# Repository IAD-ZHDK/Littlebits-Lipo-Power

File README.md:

# Littlebits Lipo Power

**A power-bit for running littlebits projects on a standard 3.7 Lipo battery with 2-pin, PH series JST connection.**

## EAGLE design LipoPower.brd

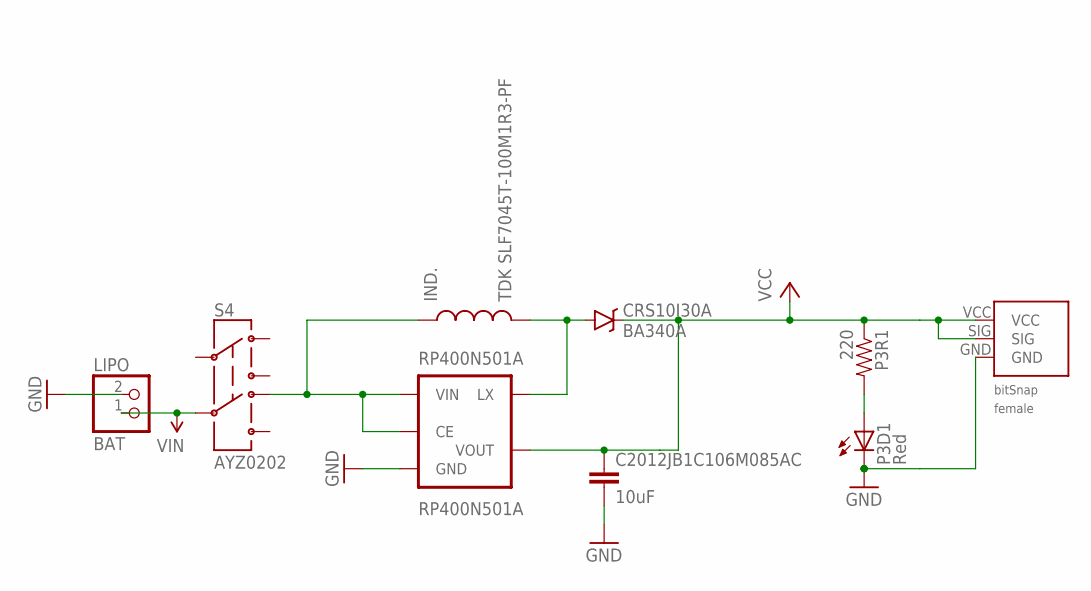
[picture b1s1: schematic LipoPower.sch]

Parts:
C2012JB1C106M085AC: 10uF; 1210
CRS10I30A: BA340A; SMA-DIODE
IND.: TDK SLF7045T-100M1R3-PF; B82462G
LIPO: BAT; JST-PH-2-SMT-RA
P3BSF1: BITSNAP_V03_FEMALE
P3D1: Red; LED-1206
P3R1: 220; 0603-RES
RP400N501A: RP400N501A; SOT23-5
S4: AYZ0202

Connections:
GND: C2012JB1C106M085AC.2, LIPO.2 (1), P3BSF1.GND, P3D1.C, RP400N501A.2 (GND)
unnamed: P3D1.A, P3R1.2
unnamed: CRS10I30A.A, IND..P$2 (2), RP400N501A.5 (LX)
unnamed: IND..P$1 (1), RP400N501A.1 (CE), RP400N501A.3 (VIN), S4.6 (4)
VCC: C2012JB1C106M085AC.1, CRS10I30A.C, P3BSF1.SIG, P3BSF1.VCC, P3R1.1, RP400N501A.4 (VOUT)
VIN: LIPO.1 (2), S4.5

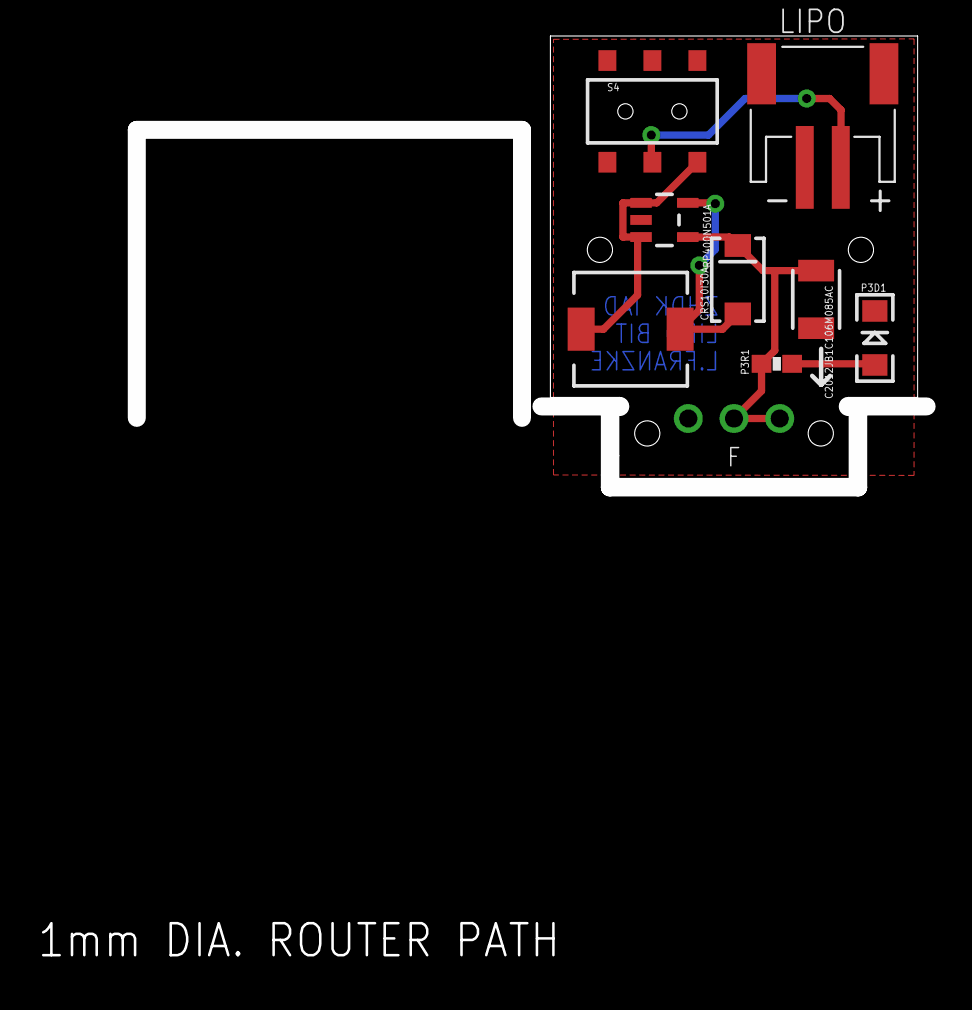
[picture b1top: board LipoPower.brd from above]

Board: 2 copper layers, 49.0 x 51.1 mm, 11 parts (0 on the bottom side), 6 nets.

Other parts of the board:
U$2: FRAME-LETTER-OHWOHW; FABDWG01-OHW
U$15: LB_PWR_LEGS

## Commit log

2018-02-09 Eagle files by Luke Franzke
2018-02-09 Moved Files
2018-02-09 readme

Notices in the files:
parts and their libraries:
SparkFun-Electromechanical: Licensing: CC v3.0 Share-Alike You are welcome to use this library for commercial purposes.
